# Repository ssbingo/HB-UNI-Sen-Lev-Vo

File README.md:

# HB-UNI-Sen-Lev-Vo
Sensor für Voltronic-Sonden

  - Votronic 12-24K
  - Votronic 15-50K
  - Votronic 30-110K
  - Votronic 20-K-WC

## Bilder

## Konfiguration
### auf der Platine

### im SourceCode

### in der CCU/Raspberymatic

## Schaltplan

[:arrow_right: Schaltplan](Images/*.pdf)

## Platine

[:arrow_right: PCB Gerber](Platine/HB-UNI-Sen-Lev-Vo.zip)

## Gehäuse

## Aufbau / Stückliste

### Der Aufbau

### Die benötigten Bauteile
| Bauteil | Link |
| --------|------|

## Hinweise

- :exclamation: 

## CCU2/CCU3/RaspberryMatic Installation

Einstellungen/Systemsteuerung/Zusatzsoftware -> Datei 

Ich nutze das AddOn von Jérôme (jp112sdl) [JP-HB-Devices-addon](https://github.com/jp112sdl/JP-HB-Devices-addon).
In dieses bzw. dessen Struckture müssen die Dateien aus dem Verzeichniss [AddOn](AddOn) entsprechend selbst eingebunden werden und das AddOn dann installiert werden.

## Benötige Libraries

  - [AskSinPP](https://github.com/pa-pa/AskSinPP)
   	- sowie die dort aufgeführten [zusätzlichen Bibliotheken](https://github.com/pa-pa/AskSinPP#required-additional-arduino-libraries)

## Lizenz

**Creative Commons BY-NC-SA**<br>
Give Credit, NonCommercial, ShareAlike

<br />This work is licensed under a <a rel="license" href="http://creativecommons.org/licenses/by-nc-sa/4.0/">Creative Commons Attribution-NonCommercial-ShareAlike 4.0 International License</a>.

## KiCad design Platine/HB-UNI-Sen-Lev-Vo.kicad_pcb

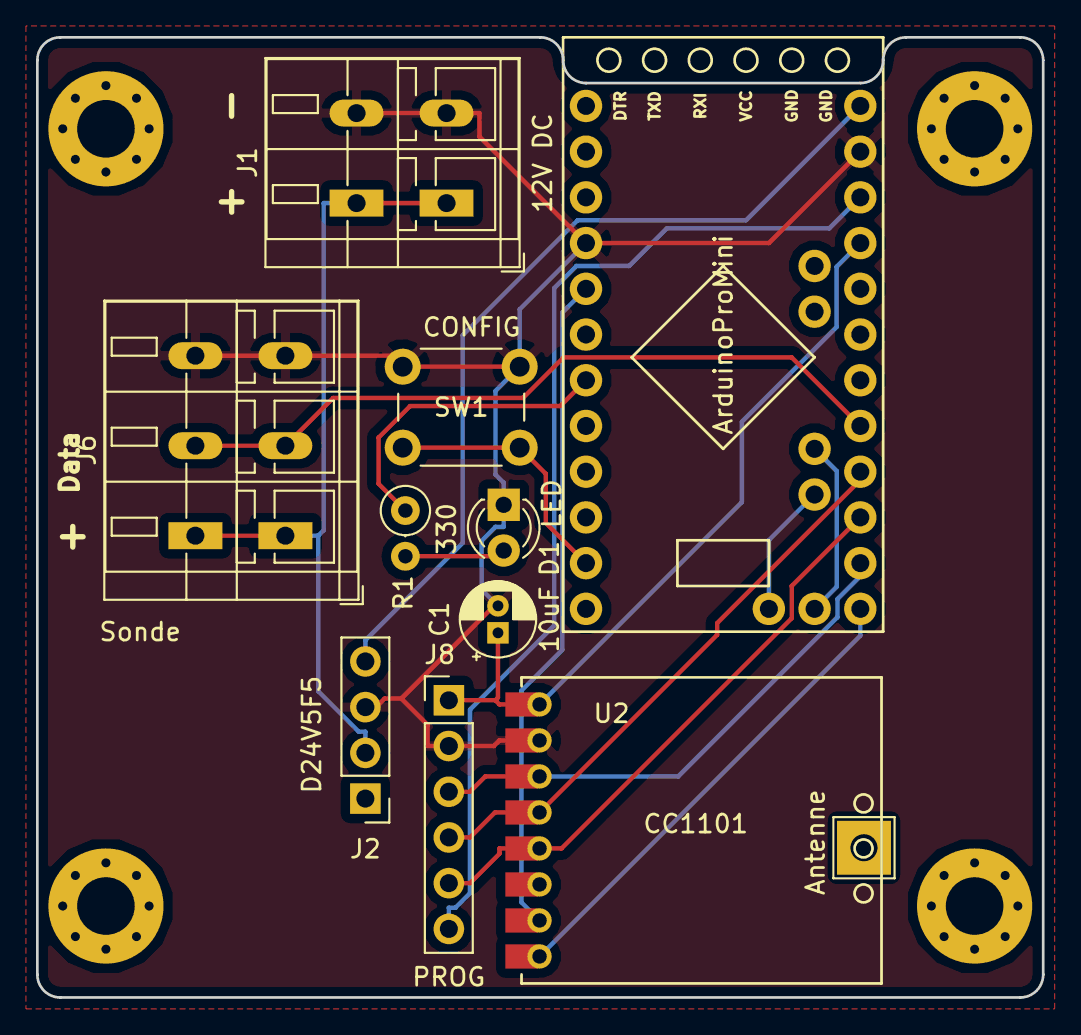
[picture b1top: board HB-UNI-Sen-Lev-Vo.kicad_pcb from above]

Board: 2 copper layers, 55.9 x 53.3 mm, 16 parts (0 on the bottom side), 14 nets.

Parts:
Antenne: TestPoint_THTPad_3.0x3.0mm_Drill1.5mm
C1: 10uF; CP_Radial_D4.0mm_P1.50mm
Copy: Version 1.0.3 - 02/2020; Copyrigth
D1: LED; LED_D3.0mm
J1: 12V DC; TerminalBlock_WAGO_236-102_1x02_P5.00mm_45Degree
J2: D24V5F5; PinHeader_1x04_P2.54mm_Vertical
J6: Sonde; TerminalBlock_WAGO_236-103_1x03_P5.00mm_45Degree
J8: PROG; PinHeader_1x06_P2.54mm_Vertical
R1: 330; R_Axial_DIN0207_L6.3mm_D2.5mm_P2.54mm_Vertical
REF01, REF02, REF03, REF04: MountingHole_3.2mm_M3_Pad_Via
SW1: CONFIG; SW_PUSH_6mm_H5mm
U1: ArduinoProMini
U2: CC1101

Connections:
+3V3: C1.1, J8.1, U1.9, U2.1
+5V: J2.4, U1.12
+12V: J1.1, J2.2, J6.1
/A0: J6.2, U1.5
/D2: U1.17, U2.7
/MISO: J8.5, U1.3, U2.5
/MOSI: J8.3, U1.2, U2.3
/RSET: J8.6, U1.10
/SCK: J8.4, U1.4, U2.4
/SS: U1.1, U2.8
GND: C1.2, D1.1, J1.2, J2.3, J6.3, J8.2, SW1.2, U1.11, U1.16, U2.2
unnamed: D1.2, R1.2
unnamed: R1.1, U1.19
unnamed: SW1.1, U1.23

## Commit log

2020-02-21 Images PCB
2020-02-21 cosmetic
2020-02-25 image Tank
2020-02-25 readme.md

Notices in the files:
Platine/HB-UNI-Sen-Lev-Vo.kicad_pcb:
© Silvio Sternitzke
